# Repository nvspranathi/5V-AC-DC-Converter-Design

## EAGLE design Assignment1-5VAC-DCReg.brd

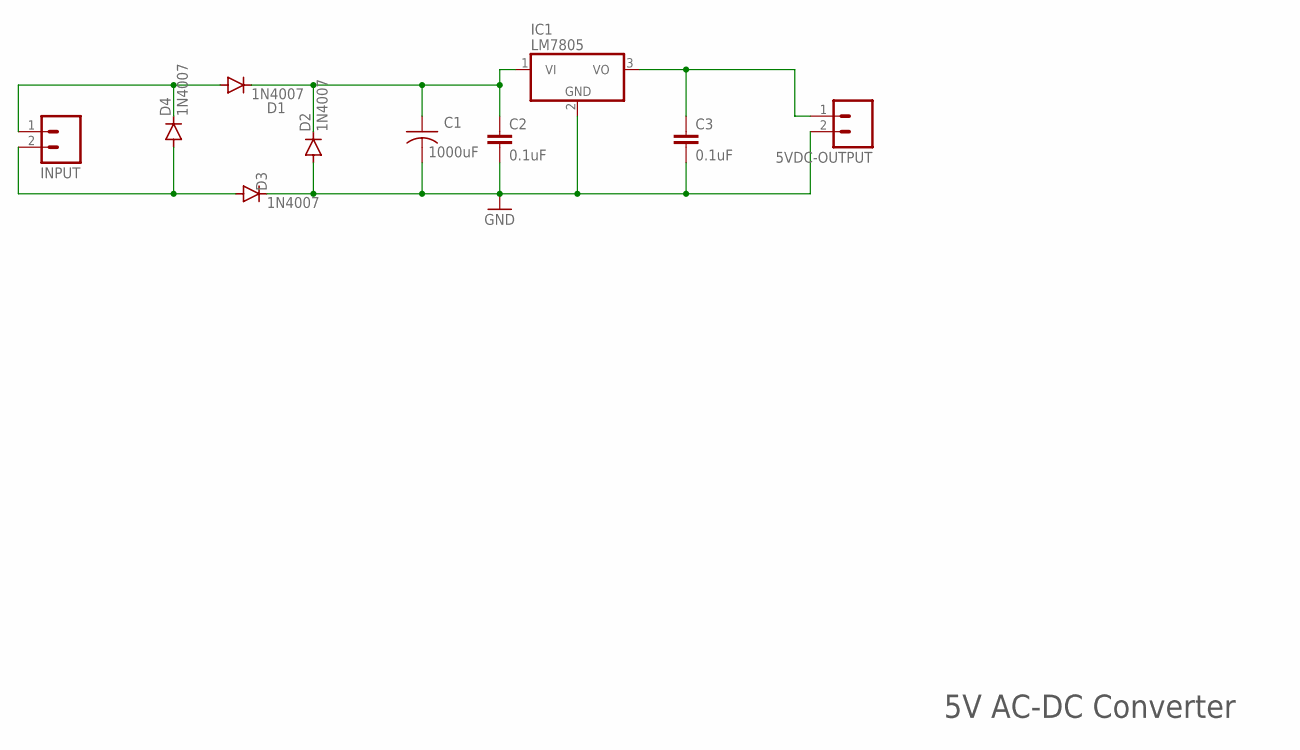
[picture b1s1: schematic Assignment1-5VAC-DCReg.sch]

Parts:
5VDC-OUTPUT: M02; 02P
C1: 1000uF; C025-024X044
C2, C3: 0.1uF; C025-025X050
D1, D2, D3, D4: 1N4007; DO41-10
IC1: LM7805; TO220V
INPUT: M02; 02P

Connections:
GND: 5VDC-OUTPUT.2, C1.2, C2.2, C3.2, D2.A, D3.C, IC1.2 (GND)
unnamed: D1.A, D4.C, INPUT.1
unnamed: D3.A, D4.A, INPUT.2
unnamed: C1.1, C2.1, D1.C, D2.C, IC1.1 (VI)
unnamed: 5VDC-OUTPUT.1, C3.1, IC1.3 (VO)

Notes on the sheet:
5V AC-DC Converter

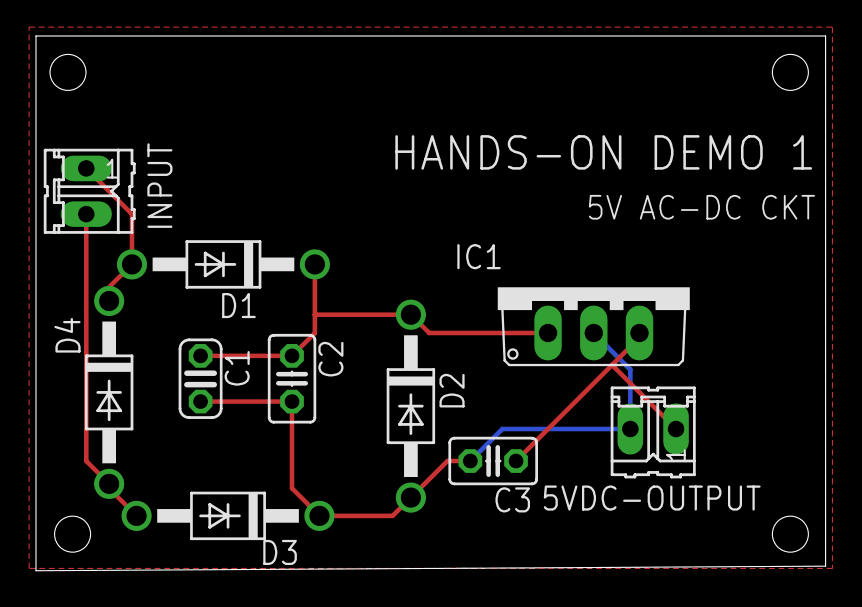
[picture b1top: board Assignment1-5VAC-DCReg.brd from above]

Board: 2 copper layers, 43.9 x 29.7 mm, 10 parts (0 on the bottom side), 5 nets.

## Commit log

2022-08-24 5V AC-DC Converter Design
